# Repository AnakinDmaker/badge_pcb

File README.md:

# Badge PCB

KiCad hardware design for a custom ESP32-based smart badge with WS2812 addressable LEDs and capacitive touch.

## Status
🚧 In Progress — schematic in development

## Specs
- ESP32 (WROOM module)
- 12–16x WS2812 addressable LEDs
- 1x capacitive touch pad
- USB-C powered
- Custom-shaped PCB, under 100×100mm

## Tools
KiCad

## Related repos
- badge-firmware — firmware for this board
- badge-web — browser-based controller

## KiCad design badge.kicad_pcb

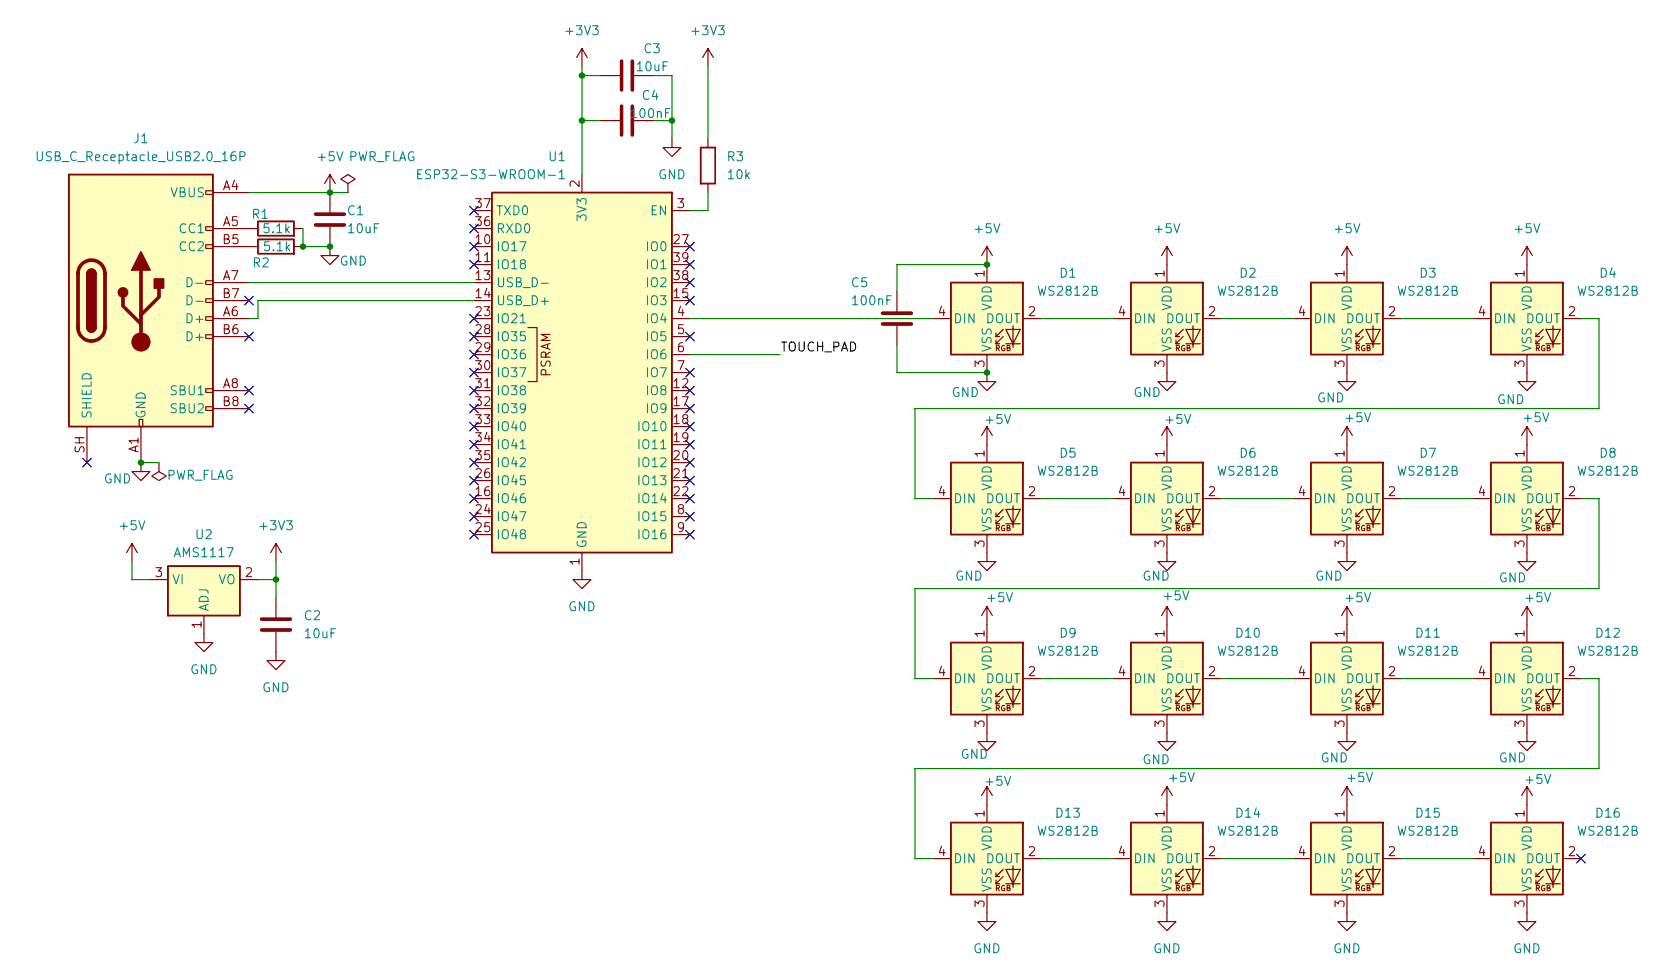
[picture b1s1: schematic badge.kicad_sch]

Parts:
C1, C2, C3: 10uF; C_0805_2012Metric
C4, C5: 100nF; C_0805_2012Metric
D1, D2, D3, D4, D5, D6, D7, D8, D9, D10, D11, D12, D13, D14, D15, D16: WS2812B; LED_WS2812B_PLCC4_5.0x5.0mm_P3.2mm
J1: USB_C_Receptacle_USB2.0_16P; USB_C_Receptacle_GCT_USB4105-xx-A_16P_TopMnt_Horizontal
R1, R2: 5.1k; R_0805_2012Metric
R3: 10k; R_0805_2012Metric
U1: ESP32-S3-WROOM-1
U2: AMS1117; SOT-223-3_TabPin2

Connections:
+3V3: C2.2, C3.2, C4.2, R3.1, U1.2 (3V3), U2.2 (VO)
+5V: C1.2, C5.2, D1.1 (VDD), D2.1 (VDD), D3.1 (VDD), D4.1 (VDD), D5.1 (VDD), D6.1 (VDD), D7.1 (VDD), D8.1 (VDD), D9.1 (VDD), D10.1 (VDD), D11.1 (VDD), D12.1 (VDD), D13.1 (VDD), D14.1 (VDD), D15.1 (VDD), D16.1 (VDD), J1.A4 (VBUS), J1.A9 (VBUS), J1.B4 (VBUS), J1.B9 (VBUS), U2.3 (VI)
/TOUCH_PAD: U1.6 (IO6)
GND: C1.1, C2.1, C3.1, C4.1, C5.1, D1.3 (VSS), D2.3 (VSS), D3.3 (VSS), D4.3 (VSS), D5.3 (VSS), D6.3 (VSS), D7.3 (VSS), D8.3 (VSS), D9.3 (VSS), D10.3 (VSS), D11.3 (VSS), D12.3 (VSS), D13.3 (VSS), D14.3 (VSS), D15.3 (VSS), D16.3 (VSS), J1.A1 (GND), J1.A12 (GND), J1.B1 (GND), J1.B12 (GND), R1.2, R2.2, U1.1 (GND), U1.40 (GND), U1.41 (GND), U2.1 (ADJ)
unnamed: D1.4 (DIN), U1.4 (IO4)
unnamed: D1.2 (DOUT), D2.4 (DIN)
unnamed: D2.2 (DOUT), D3.4 (DIN)
unnamed: D3.2 (DOUT), D4.4 (DIN)
unnamed: D4.2 (DOUT), D5.4 (DIN)
unnamed: D5.2 (DOUT), D6.4 (DIN)
unnamed: D6.2 (DOUT), D7.4 (DIN)
unnamed: D7.2 (DOUT), D8.4 (DIN)
unnamed: D8.2 (DOUT), D9.4 (DIN)
unnamed: D9.2 (DOUT), D10.4 (DIN)
unnamed: D10.2 (DOUT), D11.4 (DIN)
unnamed: D11.2 (DOUT), D12.4 (DIN)
unnamed: D12.2 (DOUT), D13.4 (DIN)
unnamed: D13.2 (DOUT), D14.4 (DIN)
unnamed: D14.2 (DOUT), D15.4 (DIN)
unnamed: D15.2 (DOUT), D16.4 (DIN)
unnamed: J1.A5 (CC1), R1.1
unnamed: J1.B5 (CC2), R2.1
unnamed: R3.2, U1.3 (EN)
unnamed: J1.A6 (D+), U1.14 (USB_D+)
unnamed: J1.A7 (D-), U1.13 (USB_D-)

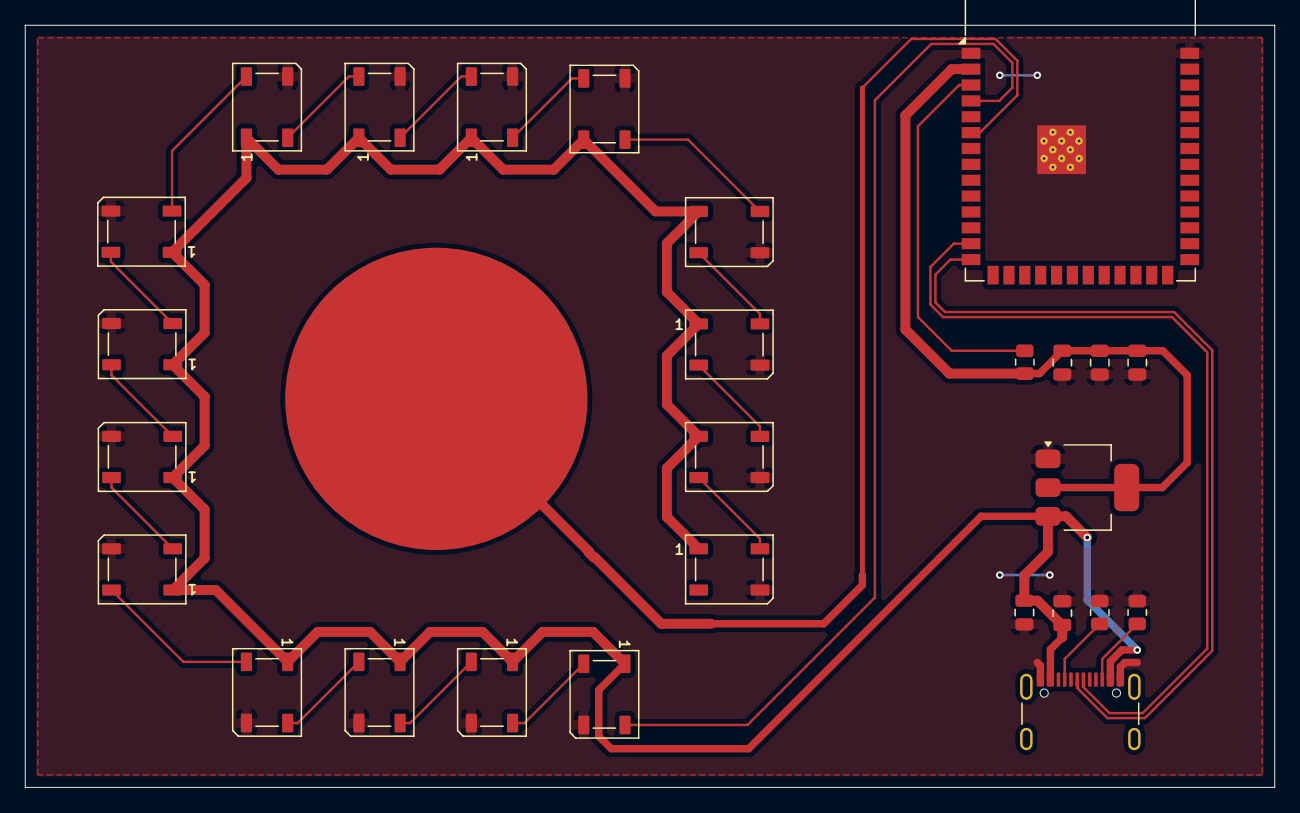
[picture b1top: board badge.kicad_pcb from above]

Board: 2 copper layers, 100.0 x 61.0 mm, 27 parts (0 on the bottom side), 24 nets.
